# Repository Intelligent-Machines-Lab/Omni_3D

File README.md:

# Omni
Code for omnidirectional robot with Intel Realsense for Slam

Still in development.

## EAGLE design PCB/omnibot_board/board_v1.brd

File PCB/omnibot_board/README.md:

# Omni board
The OMNI board manages power supply to the camera mount and allows communication between Arduino Nano and the camera rotation motor.

-----------------

## Schematic

Click [here](https://github.com/Intelligent-Machines-Lab/Omni_3D/blob/master/PCB/omnibot_board/board_v1.pdf) to open the schematic pdf. 

<div align="center">
  <b>
</div>

## PCB

<div align="center">
  <b>
</div>

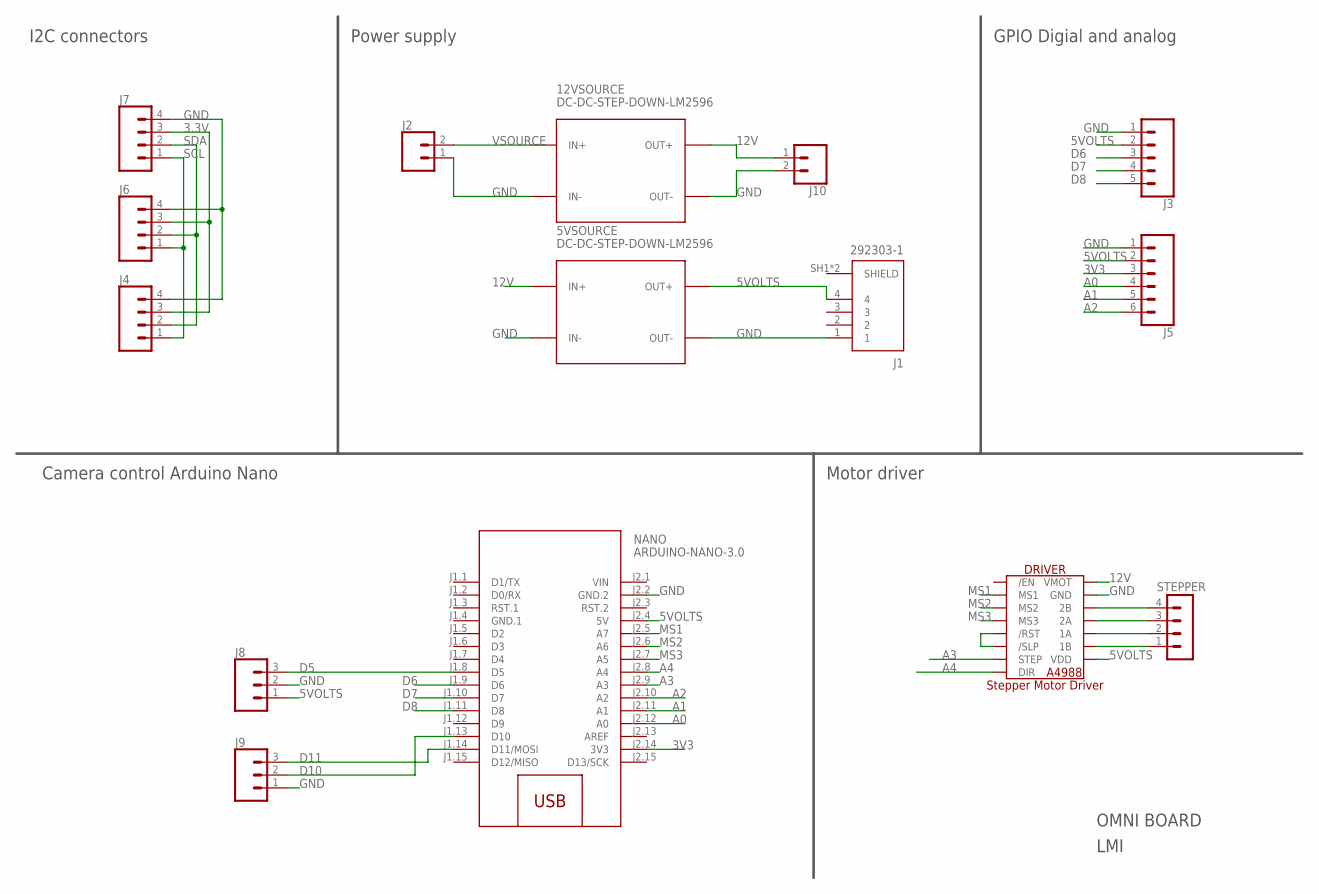
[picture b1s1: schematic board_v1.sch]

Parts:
5VSOURCE, 12VSOURCE: DC-DC-STEP-DOWN-LM2596
DRIVER: A4988_STEP
J1: 292303-1
J2, J10: CONN_025MM; SCREWTERMINAL-5MM-2
J3: CONN_05; 1X05
J4, J6, J7: CONN_04POLAR; MOLEX-1X4
J5: CONN_06SILK_FEMALE_PTH; 1X06
J8, J9: CONN_03POLAR; MOLEX-1X3
NANO: ARDUINO-NANO-3.0
STEPPER: MA04-1

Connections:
3.3V: J4.3, J6.3, J7.3
3V3: J5.3, NANO.J2.14 (3V3)
5VOLTS: 5VSOURCE.OUT+, DRIVER.VDD, J1.4, J3.2, J5.2, J8.1, NANO.J2.4 (5V)
12V: 5VSOURCE.IN+, 12VSOURCE.OUT+, DRIVER.VMOT, J10.1
A0: J5.4, NANO.J2.12 (A0)
A1: J5.5, NANO.J2.11 (A1)
A2: J5.6, NANO.J2.10 (A2)
A3: DRIVER.STEP, NANO.J2.9 (A3)
A4: DRIVER.DIR, NANO.J2.8 (A4)
D5: J8.3, NANO.J1.8 (D5)
D6: J3.3, NANO.J1.9 (D6)
D7: J3.4, NANO.J1.10 (D7)
D8: J3.5, NANO.J1.11 (D8)
D10: J9.2, NANO.J1.13 (D10)
D11: J9.3, NANO.J1.14 (D11/MOSI)
GND: 5VSOURCE.IN-, 5VSOURCE.OUT-, 12VSOURCE.IN-, 12VSOURCE.OUT-, DRIVER.GND, DRIVER.GND2 (GND), J1.1, J2.1, J3.1, J4.4, J5.1, J6.4, J7.4, J8.2, J9.1, J10.2, NANO.J2.2 (GND.2)
GND.1: NANO.J1.4 (GND.1)
MS1: DRIVER.MS1, NANO.J2.5 (A7)
MS2: DRIVER.MS2, NANO.J2.6 (A6)
MS3: DRIVER.MS3, NANO.J2.7 (A5)
unnamed: DRIVER.2B, STEPPER.4
unnamed: DRIVER.2A, STEPPER.3
unnamed: DRIVER.1A, STEPPER.2
unnamed: DRIVER.1B, STEPPER.1
unnamed: DRIVER./RST, DRIVER./SLP
SCL: J4.1, J6.1, J7.1
SDA: J4.2, J6.2, J7.2
SHIELD: J1.SH1 (SHIELD), J1.SH2 (SHIELD)
VSOURCE: 12VSOURCE.IN+, J2.2, NANO.J2.1 (VIN)

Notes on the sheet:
I2C connectors
Power supply
GPIO Digial and analog
Camera control Arduino Nano
Motor driver
OMNI BOARD
LMI

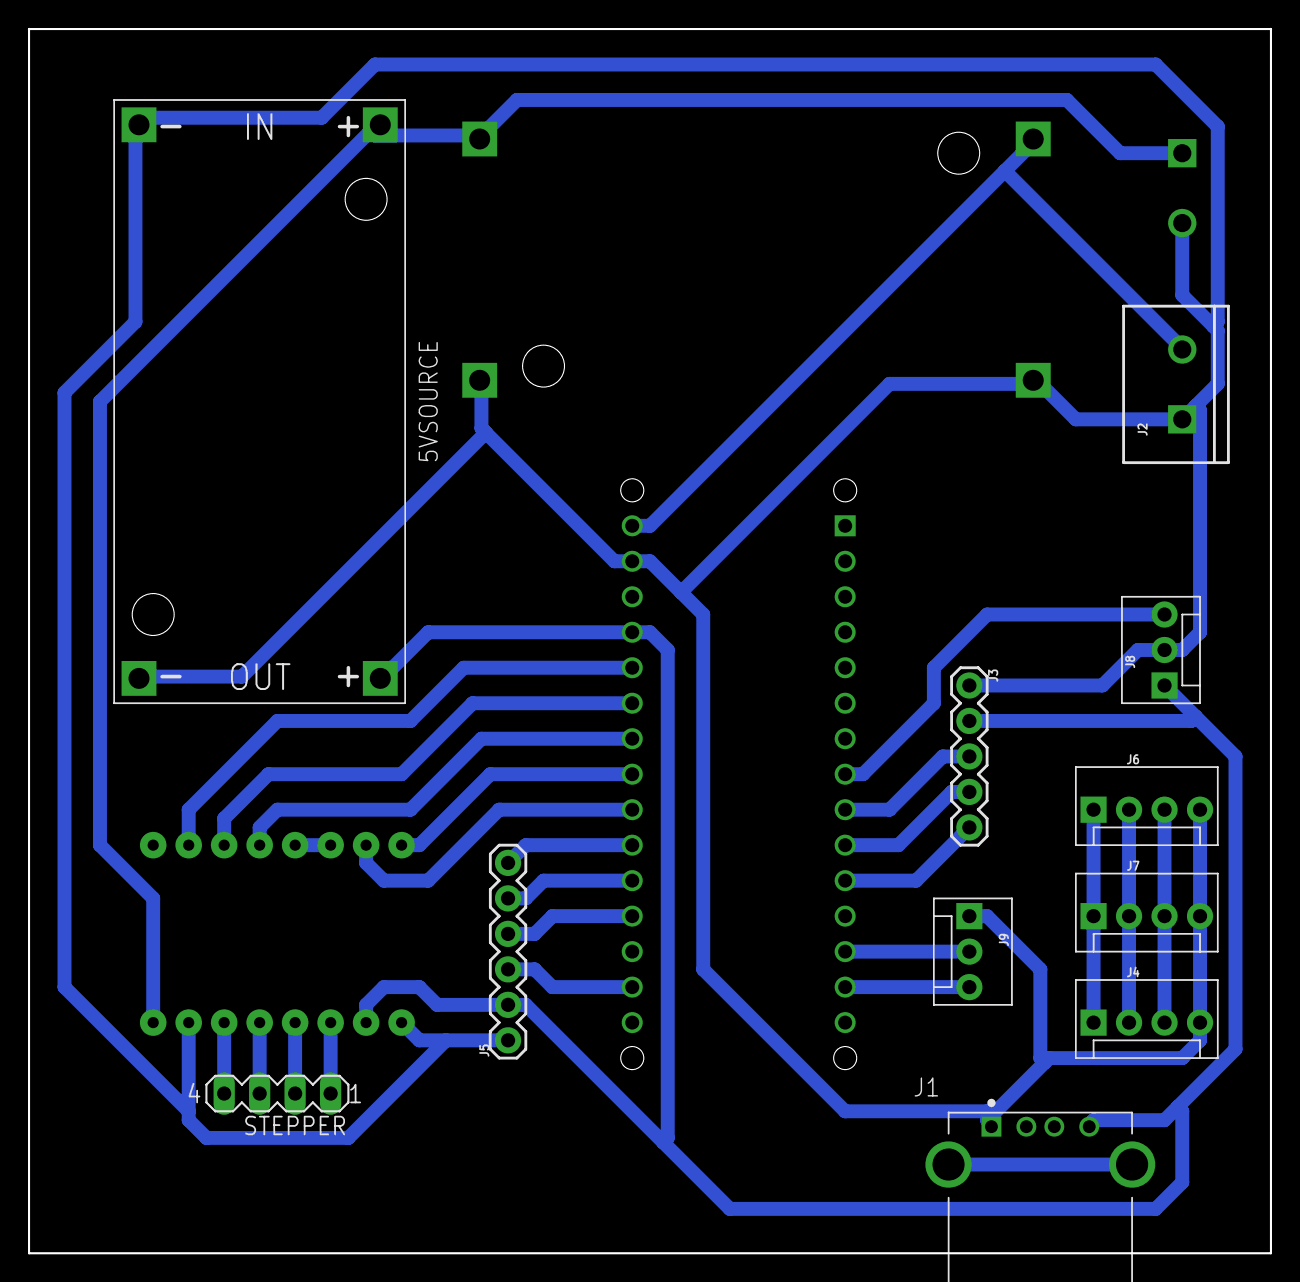
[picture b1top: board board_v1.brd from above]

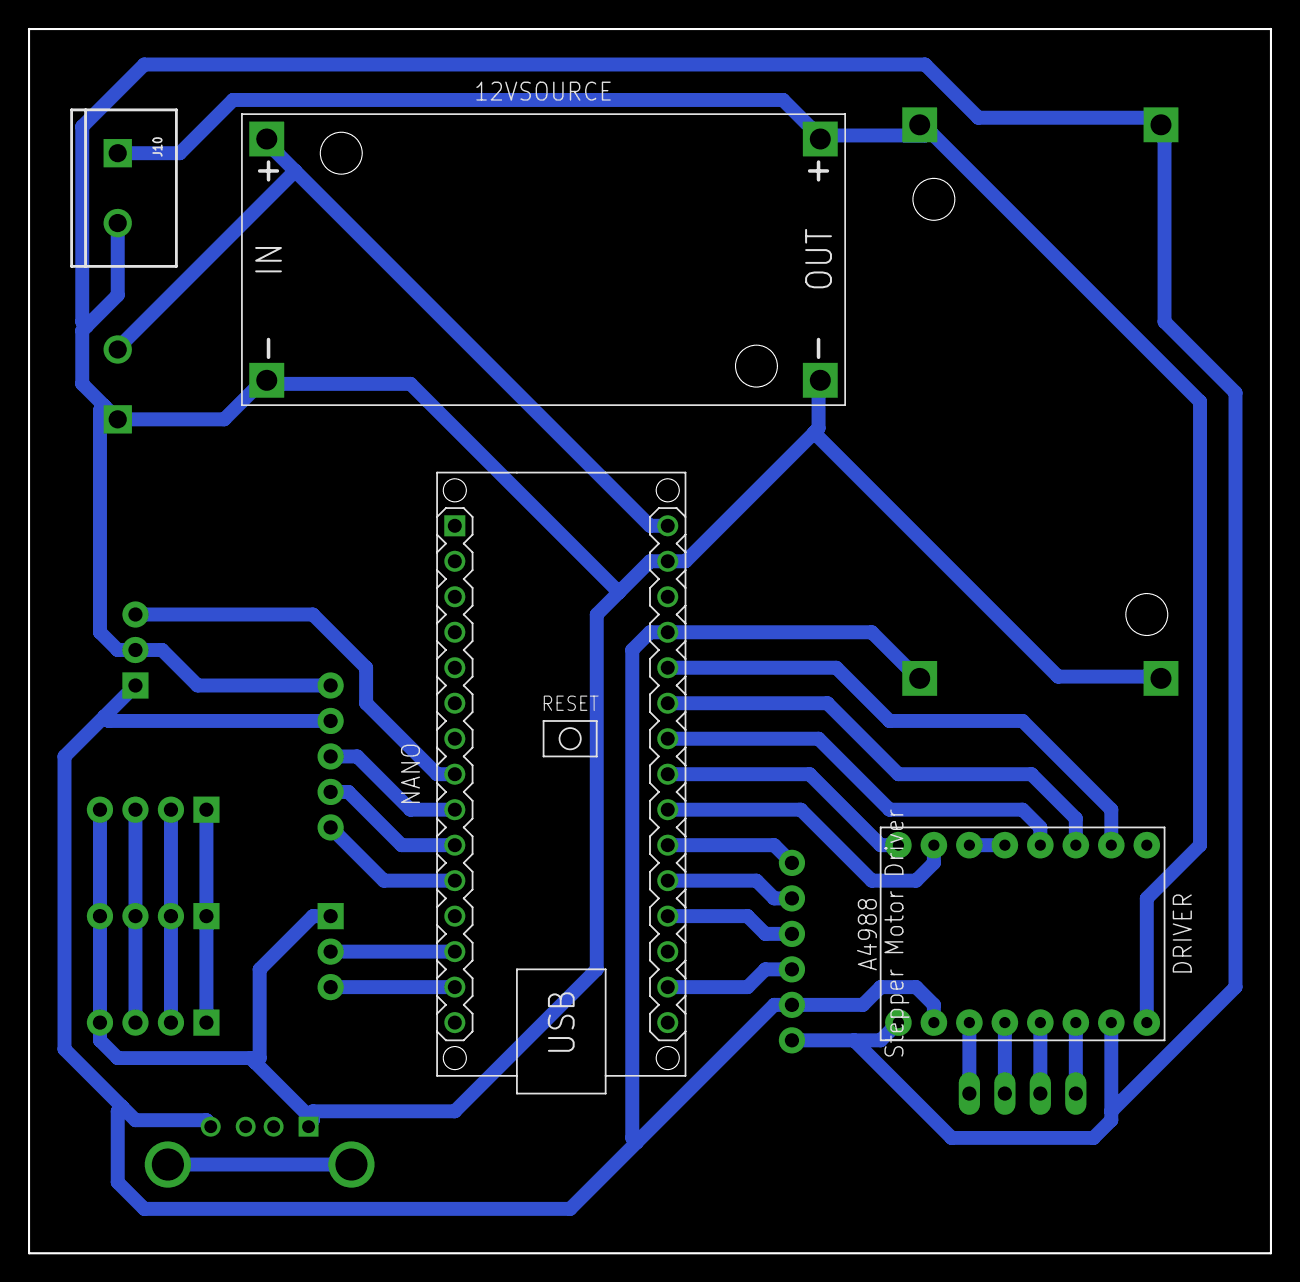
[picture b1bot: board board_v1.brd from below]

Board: 2 copper layers, 88.9 x 87.6 mm, 15 parts (4 on the bottom side), 28 nets.

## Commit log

2020-07-03 Added Arduino code
2020-07-07 added PCB
2020-07-09 New version for OMNI board
2020-07-09 Added schematic pdf
2020-07-11 changed v1 board
2020-07-11 Added readme v1
2020-07-11 added v2 board
2020-07-24 added point cloud generation with color and depth as input
2020-07-25 added gazebo images and planar ransac tests
2020-07-25 Added post-processing during image acquisition
2020-07-26 Starting test with semantic segmentation
2020-07-27 modifications in visual odometry
2020-07-28 added linux path
2020-07-28 added voxalization tests
2020-07-30 Preprocessing data done
2020-07-31 training with gpu
2020-07-31 Board updated
2020-07-31 Board schematic updated
2020-08-01 added trained net
2020-08-01 added image segmentation with depth data
2020-08-04 added masks
2020-08-07 added tests in a simple environment
2020-08-11 added test with canny edge detector
2020-08-14 Test with recursive RANSAC
2020-08-15 PCA bounded box
2020-09-03 Add Local Scene class
2020-09-03 Added clustring in the local scene
2020-09-05 add scene construction
2020-09-08 added proprieties gui
2020-09-10 Add roundness detection
2020-09-25 prepared for gazebo simulation
2020-09-25 Reorganized folders
2020-09-30 stating localization problem
2020-09-30 add visualization
2020-10-08 add data association
2020-10-17 Data association almost good
2020-10-19 add simple plane representation
2020-10-21 represent a plane by meshes
2020-10-28 Add cuboid
2020-11-19 add real dataset
2020-11-21 add map cleanning
2020-11-25 add odometer class
2020-11-29 add weighted mean for planes equation
2020-12-08 add kalman propagation
2020-12-08 add matplotlib plot
2020-12-11 add ekf observation model
2020-12-13 finish not-working ekf implementation
2020-12-14 ekf working
2020-12-17 change g function
2020-12-20 add point ekf, not tested yet
2021-02-11 cylinder ekf working good
2021-02-11 working big planes
2021-02-13 add more tests
2021-02-22 só desgraça hoje
2021-02-24 Use controid from plane as feature
2021-03-30 change plane representation to four parameters
2021-04-08 testing with theta dif from zero
2021-04-08 make this almost work
2021-04-09 enable two types of plane features
2021-04-09 more tests
2021-04-20 fix recursive error
2021-04-21 going for experiments
2021-04-23 add experimental implementation
2021-04-24 experimental working
2021-05-01 add point bucket
2021-05-12 add point representation after ekf correction
2021-05-19 cuboid ready
2021-05-20 added cuboid on global map
2021-06-22 Incorporate octree and voxelgrid
2021-06-23 no success in converting octree to voxel grid =(
2021-06-28 start independent octree representation for each feature
2021-07-07 add memory log for pcd, octree and point cloud
2021-07-08 add log for high and low level world
2021-07-10 add log analisys
2021-07-13 add time log
2021-07-14 add time-memory plot

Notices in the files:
parts and their libraries:
diy-modules: Released under the Creative Commons Attribution 4.0 International License: http://creativecommons.org/licenses/by/4.0
SparkFun-Connectors: Licensing: Creative Commons ShareAlike 4.0 International - https://creativecommons.org/licenses/by-sa/4.0
